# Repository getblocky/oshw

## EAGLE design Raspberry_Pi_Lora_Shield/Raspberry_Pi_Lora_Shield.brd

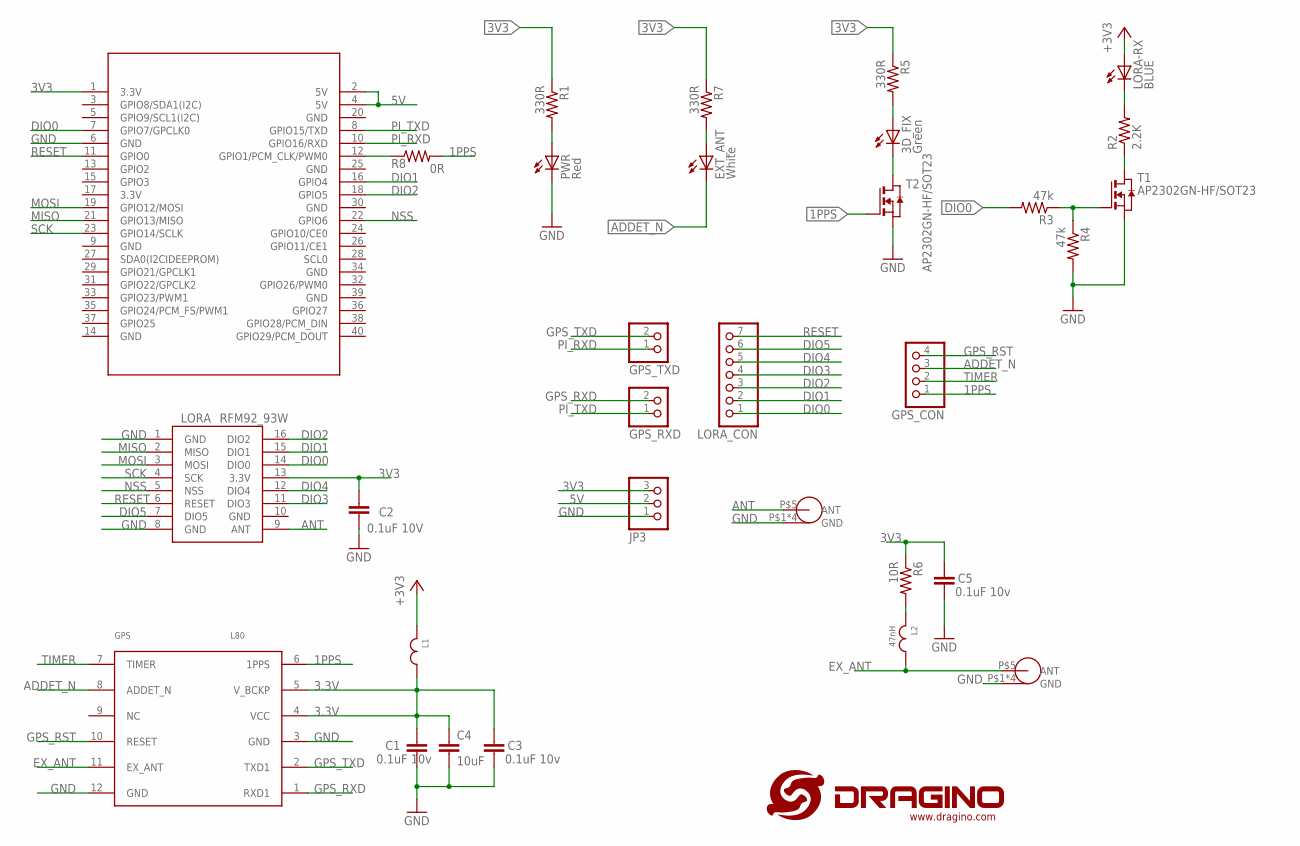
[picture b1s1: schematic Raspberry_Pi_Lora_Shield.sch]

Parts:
3D_FIX: Green; CHIPLED_0603
C1, C3, C5: 0.1uF 10v; C0603
C2: 0.1uF 10V; C0603
C4: 10uF; C1206K
EXT_ANT: White; CHIPLED_0603
GPS: L80
GPS_ANT: NL; SMA-KE
GPS_CON: PINHD-1X4; 1X04
GPS_RXD: PINHD-1X2; 1X02
GPS_TXD: PINHD-1X2; 1X02
JP3: PINHD-1X3; 1X03
L1: JLC-PZ2012D800-3R0TF; C0805
L2: 47nH; C0402
LORA: RFM92_93W
LORA-RX: BLUE; CHIPLED_0603
LORA_ANT: SMA-KE
LORA_CON: PINHD-1X7; 1X07
PWR: Red; CHIPLED_0603
R1, R5, R7: 330R; R0603
R2: 2.2K; R0603
R3, R4: 47k; R0603
R6: 10R; R0603
R8: 0R; R0805
T1, T2: AP2302GN-HF/SOT23; SOT-23
U$1: LOGO-NEW; LOGO-SILK-NEW
U$2: RPILORASHIELD

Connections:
1PPS: GPS.6 (1PPS), GPS_CON.1, R8.2, T2.3 (G)
3.3V: C1.2, C3.2, C4.1, GPS.4 (VCC), GPS.5 (V_BCKP), L1.2
3V3: C2.2, C5.2, JP3.3, L1.1, LORA.13 (3.3V), LORA-RX.A, R1.1, R5.1, R6.1, R7.1, U$2.1 (3.3V)
5V: JP3.2, U$2.2 (5V), U$2.4 (5V)
/RESET: R2.1, T1.1 (D)
ADDET_N: EXT_ANT.C, GPS.8 (ADDET_N), GPS_CON.3
ANT: LORA.9 (ANT), LORA_ANT.P$5 (ANT)
DIO0: LORA.14 (DIO0), LORA_CON.1, R3.2, U$2.7 (GPIO7/GPCLK0)
DIO1: LORA.15 (DIO1), LORA_CON.2, U$2.16 (GPIO4)
DIO2: LORA.16 (DIO2), LORA_CON.3, U$2.18 (GPIO5)
DIO3: LORA.11 (DIO3), LORA_CON.4
DIO4: LORA.12 (DIO4), LORA_CON.5
DIO5: LORA.7 (DIO5), LORA_CON.6
EX_ANT: GPS.11 (EX_ANT), GPS_ANT.P$5 (ANT), L2.2
GND: C1.1, C2.1, C3.1, C4.2, C5.1, GPS.3 (GND), GPS.12 (GND), GPS_ANT.P$1 (GND), GPS_ANT.P$2 (GND), GPS_ANT.P$3 (GND), GPS_ANT.P$4 (GND), JP3.1, LORA.1 (GND), LORA.8 (GND), LORA.10 (GND), LORA_ANT.P$1 (GND), LORA_ANT.P$2 (GND), LORA_ANT.P$3 (GND), LORA_ANT.P$4 (GND), PWR.C, R4.2, T1.2 (S), T2.2 (S), U$2.6 (GND)
GPS_RST: GPS.10 (RESET), GPS_CON.4
GPS_RXD: GPS.1 (RXD1), GPS_RXD.2
GPS_TXD: GPS.2 (TXD1), GPS_TXD.2
MISO: LORA.2 (MISO), U$2.21 (GPIO13/MISO)
MOSI: LORA.3 (MOSI), U$2.19 (GPIO12/MOSI)
unnamed: R3.1, R4.1, T1.3 (G)
unnamed: 3D_FIX.A, R5.2
unnamed: 3D_FIX.C, T2.1 (D)
unnamed: L2.1, R6.2
unnamed: EXT_ANT.A, R7.2
unnamed: PWR.A, R1.2
unnamed: R8.1, U$2.12 (GPIO1/PCM_CLK/PWM0)
unnamed: LORA-RX.C, R2.2
NSS: LORA.5 (NSS), U$2.22 (GPIO6)
PI_RXD: GPS_TXD.1, U$2.10 (GPIO16/RXD)
PI_TXD: GPS_RXD.1, U$2.8 (GPIO15/TXD)
RESET: LORA.6 (RESET), LORA_CON.7, U$2.11 (GPIO0)
SCK: LORA.4 (SCK), U$2.23 (GPIO14/SCLK)
TIMER: GPS.7 (TIMER), GPS_CON.2

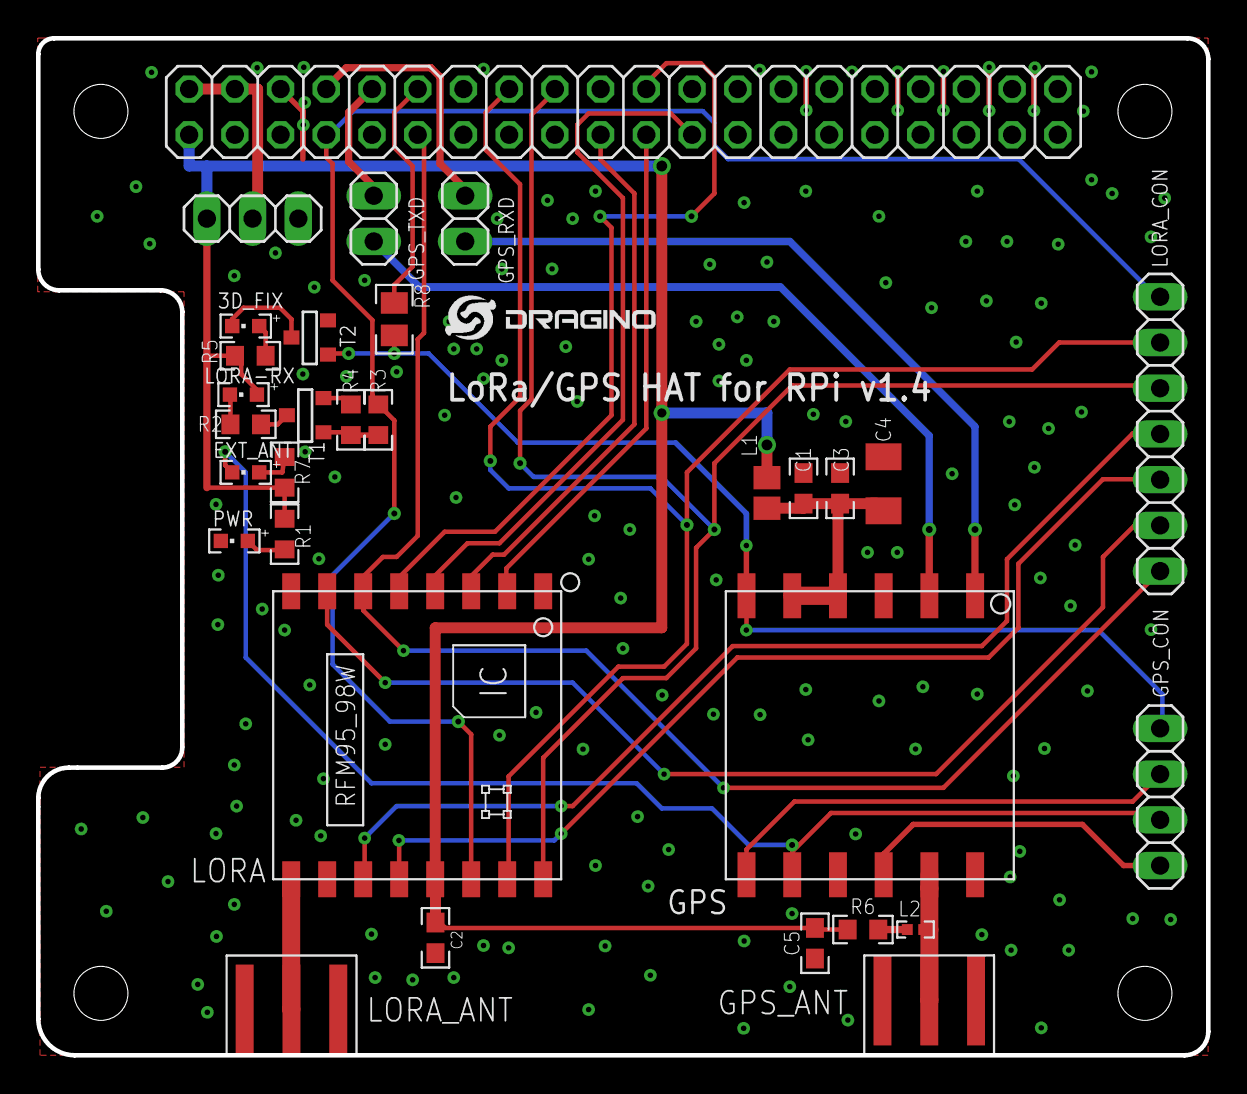
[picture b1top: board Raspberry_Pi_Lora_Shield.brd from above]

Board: 2 copper layers, 65.0 x 56.5 mm, 33 parts (1 on the bottom side), 34 nets.

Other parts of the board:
U$3: BLOCKY_LOGO

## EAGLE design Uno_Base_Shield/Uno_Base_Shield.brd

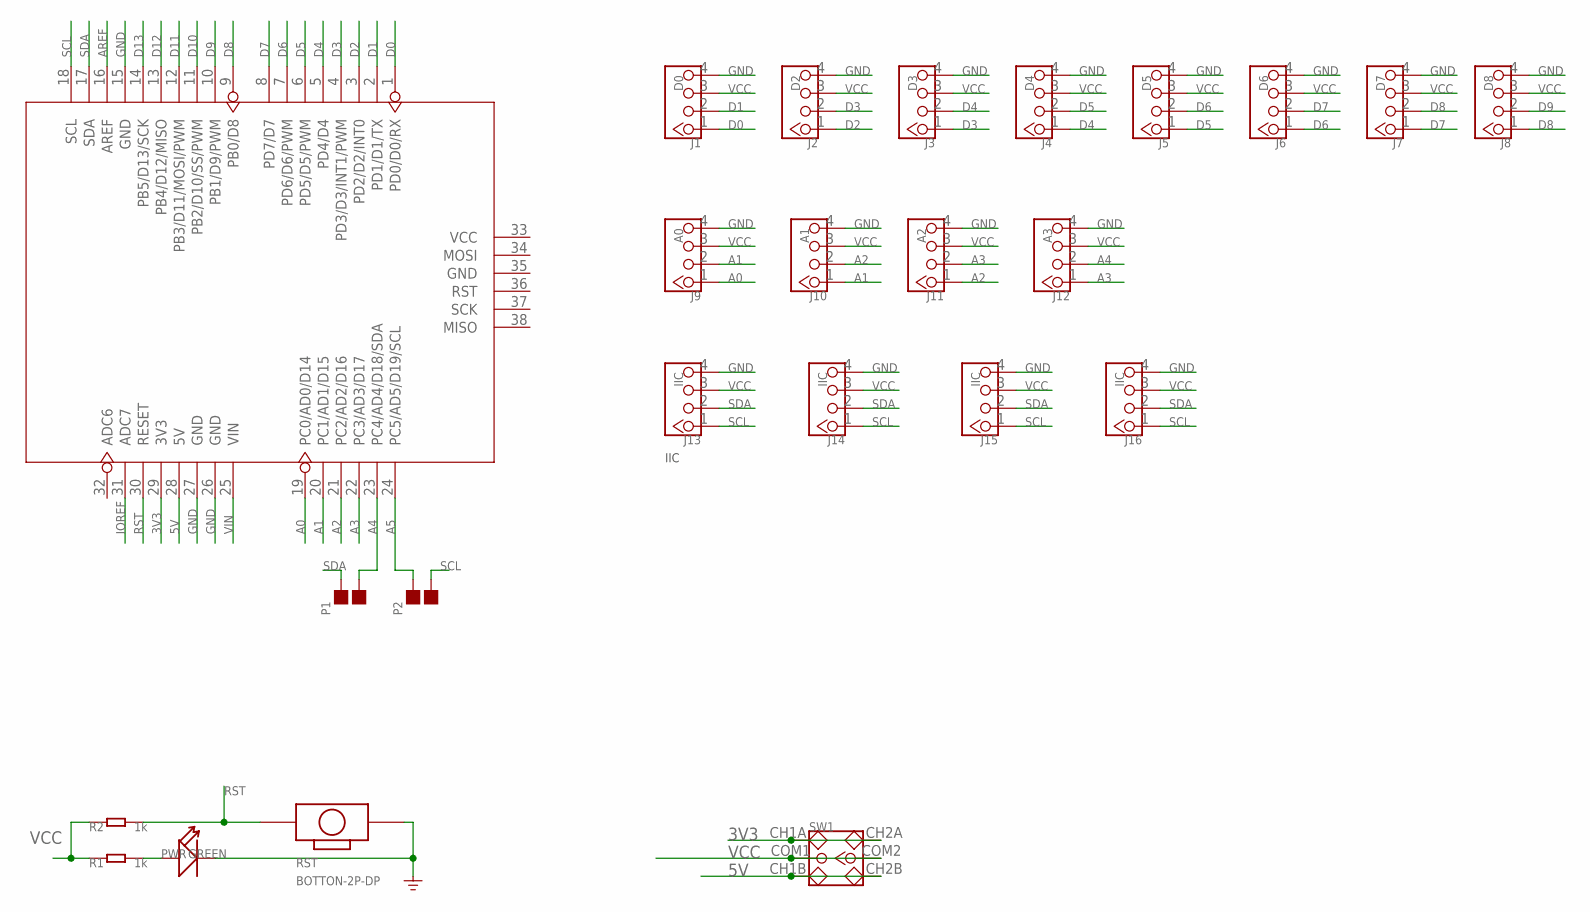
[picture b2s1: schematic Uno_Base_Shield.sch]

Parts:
J1: D0; 4P-2.0
J2: D2; 4P-2.0
J3: D3; 4P-2.0
J4: D4; 4P-2.0
J5: D5; 4P-2.0
J6: D6; 4P-2.0
J7: D7; 4P-2.0
J8: D8; 4P-2.0
J9: A0; 4P-2.0-90D
J10: A1; 4P-2.0-90D
J11: A2; 4P-2.0-90D
J12: A3; 4P-2.0-90D
J13, J14, J15, J16: IIC; 4P-2.0
P1, P2: DNP; 2P-SMD-1.78X1.27
PWR: GREEN; LED-2P-2.54-3MM
R1, R2: 1k; R0603
RST: BOTTON-2P-DP; 2P-7.62X3.56-90D
SW1: SWITCH-2CH-6P'90D'; 6P-2CH-2.5-9.1X3.5X3.2H-90D
U2: DIP Long Blue Female Header; ARDUINO-38P

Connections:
3V3: SW1.CH1A, SW1.CH2A, U2.29 (3V3)
5V: SW1.CH1B, SW1.CH2B, U2.28 (5V)
A0: J9.1, U2.19 (PC0/AD0/D14)
A1: J9.2, J10.1, U2.20 (PC1/AD1/D15)
A2: J10.2, J11.1, U2.21 (PC2/AD2/D16)
A3: J11.2, J12.1, U2.22 (PC3/AD3/D17)
A4: J12.2, P1.1, U2.23 (PC4/AD4/D18/SDA)
A5: P2.2, U2.24 (PC5/AD5/D19/SCL)
AREF: U2.16 (AREF)
D0: J1.1, U2.1 (PD0/D0/RX)
D1: J1.2, U2.2 (PD1/D1/TX)
D2: J2.1, U2.3 (PD2/D2/INT0)
D3: J2.2, J3.1, U2.4 (PD3/D3/INT1/PWM)
D4: J3.2, J4.1, U2.5 (PD4/D4)
D5: J4.2, J5.1, U2.6 (PD5/D5/PWM)
D6: J5.2, J6.1, U2.7 (PD6/D6/PWM)
D7: J6.2, J7.1, U2.8 (PD7/D7)
D8: J7.2, J8.1, U2.9 (PB0/D8)
D9: J8.2, U2.10 (PB1/D9/PWM)
D10: U2.11 (PB2/D10/SS/PWM)
D11: U2.12 (PB3/D11/MOSI/PWM)
D12: U2.13 (PB4/D12/MISO)
D13: U2.14 (PB5/D13/SCK)
GND: J1.4, J2.4, J3.4, J4.4, J5.4, J6.4, J7.4, J8.4, J9.4, J10.4, J11.4, J12.4, J13.4, J14.4, J15.4, J16.4, PWR.K (-), RST.P$2 (2), U2.15 (GND), U2.26 (GND), U2.27 (GND)
IOREF: U2.31 (ADC7)
unnamed: PWR.A (+), R1.2
RST: R2.2, RST.P$1 (1), U2.30 (RESET)
SCL: J13.1, J14.1, J15.1, J16.1, P2.1, U2.18 (SCL)
SDA: J13.2, J14.2, J15.2, J16.2, P1.2, U2.17 (SDA)
VCC: J1.3, J2.3, J3.3, J4.3, J5.3, J6.3, J7.3, J8.3, J9.3, J10.3, J11.3, J12.3, J13.3, J14.3, J15.3, J16.3, R1.1, R2.1, SW1.COM1, SW1.COM2
VIN: U2.25 (VIN)

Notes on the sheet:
IIC

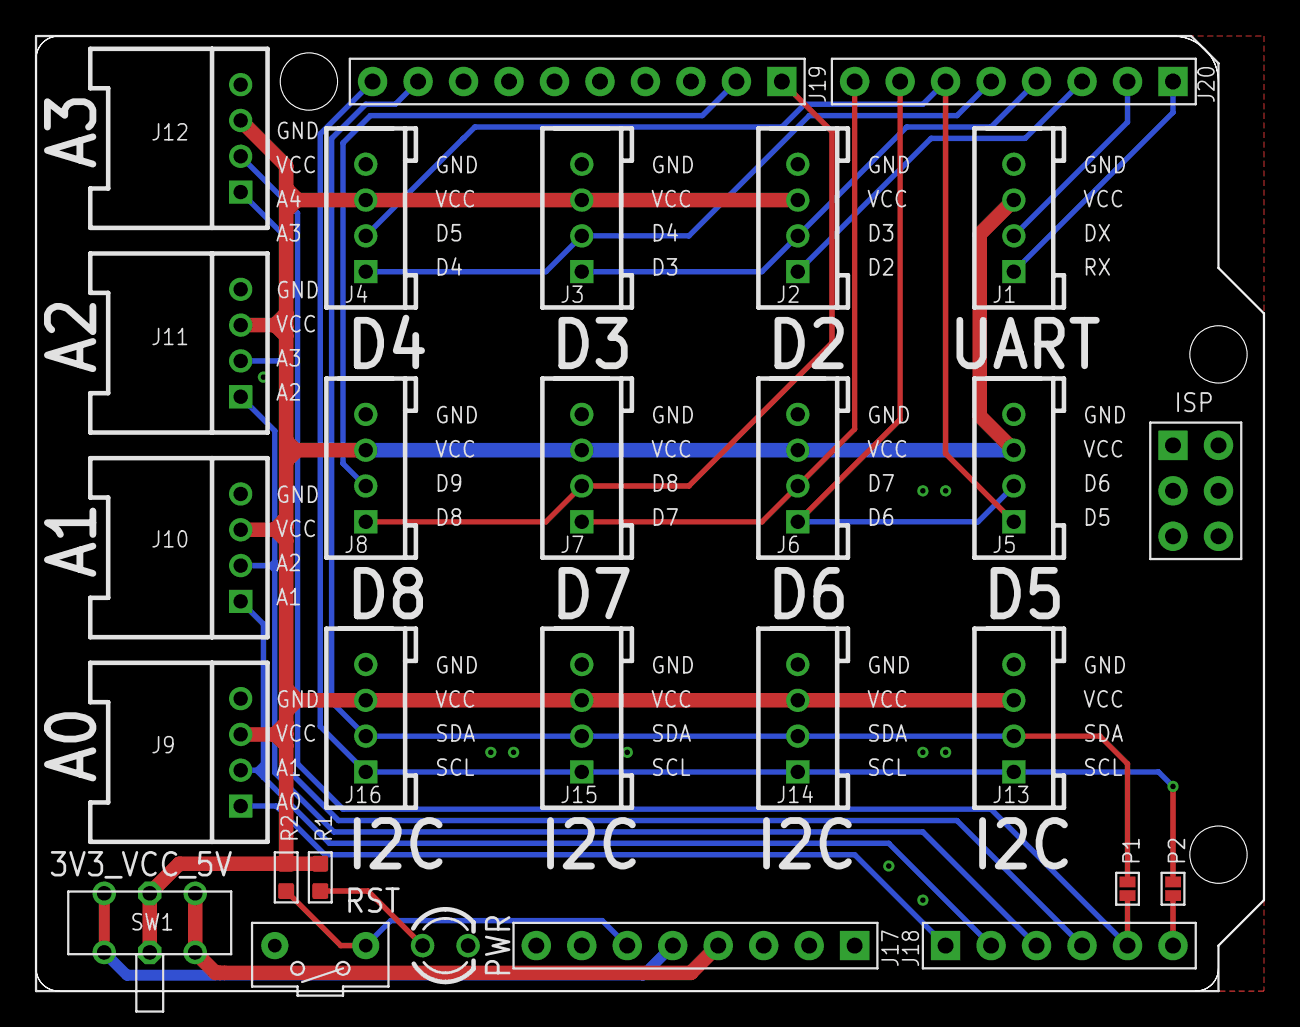
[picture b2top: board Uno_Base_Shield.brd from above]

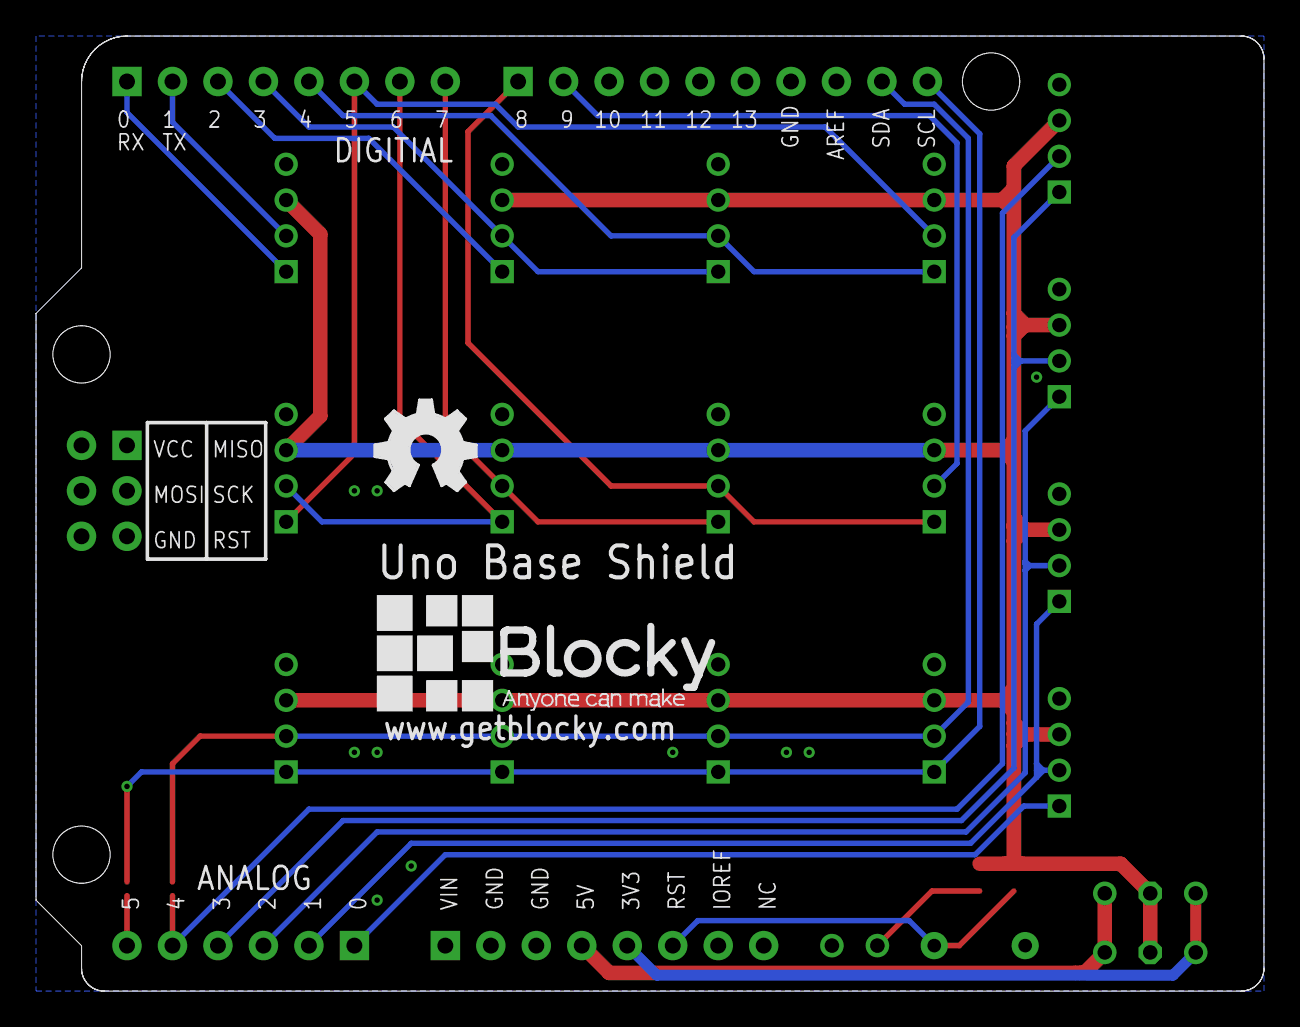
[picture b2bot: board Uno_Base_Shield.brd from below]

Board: 2 copper layers, 68.6 x 53.3 mm, 26 parts (2 on the bottom side), 24 nets.

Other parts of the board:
U$2: OSHW_FILLX200_NOTEXT
U$4: BLOCKY_LOGO

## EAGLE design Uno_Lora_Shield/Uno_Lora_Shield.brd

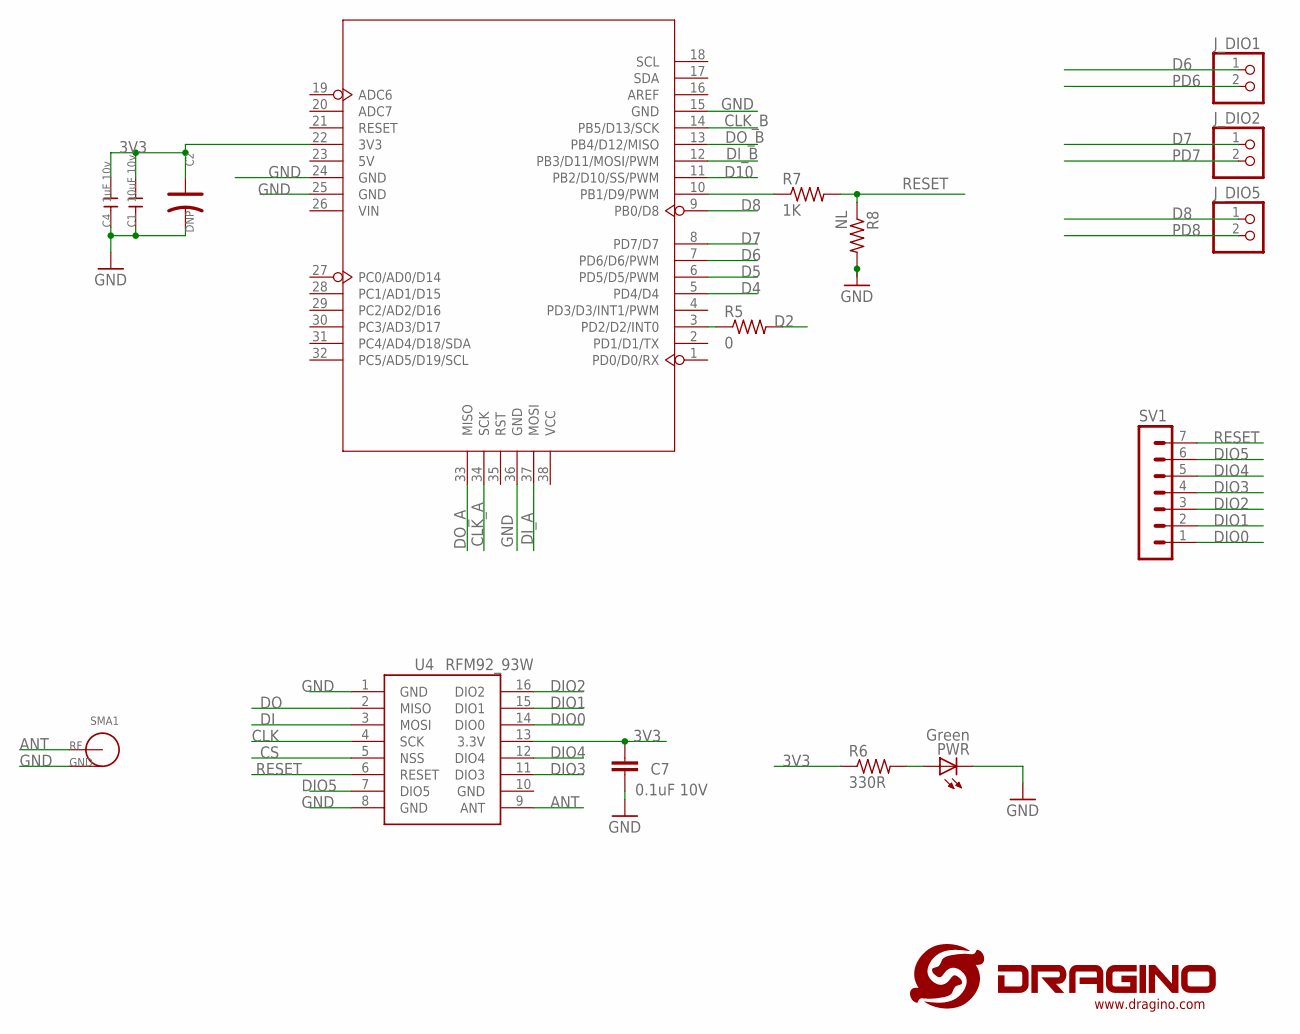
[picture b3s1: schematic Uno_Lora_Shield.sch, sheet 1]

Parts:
C1: 10uF 10v; C0805
C2: DNP; AVX-A
C4: 1uF 10v; C0805
C7: 0.1uF 10V; C0603
J_DIO1, J_DIO2, J_DIO5: PINHD-1X2; 1X02
PWR: Green; CHIP-LED0603
R5: 0; R0603
R6: 330R; R0603
R7: 1K; R0603
R8: NL; R0603
SMA1: SMA-KWE
SV1: MA07-1
U4: RFM92_93W
U5: MOUDLE_ARDUINO-38P328P_NO_VIA; MOUDLE_ARDUINO-328P--
U$1: LOGO-NEW; LOGO-SILK-NEW

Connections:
3V3: C1.2, C2.+, C4.2, C7.2, R6.1, U4.13 (3.3V), U5.22 (3V3); also elsewhere on the board
ANT: SMA1.1 (SIG), U4.9 (ANT)
CLK: U4.4 (SCK); also elsewhere on the board
CLK_A: U5.34 (SCK); also elsewhere on the board
CLK_B: U5.14 (PB5/D13/SCK); also elsewhere on the board
CS: U4.5 (NSS); also elsewhere on the board
D2: R5.2; also elsewhere on the board
D4: U5.5 (PD4/D4); also elsewhere on the board
D5: U5.6 (PD5/D5/PWM); also elsewhere on the board
D6: J_DIO1.1, U5.7 (PD6/D6/PWM)
D7: J_DIO2.1, U5.8 (PD7/D7)
D8: J_DIO5.1, U5.9 (PB0/D8)
D10: U5.11 (PB2/D10/SS/PWM); also elsewhere on the board
DI: U4.3 (MOSI); also elsewhere on the board
DIO0: SV1.1, U4.14 (DIO0); also elsewhere on the board
DIO1: SV1.2, U4.15 (DIO1); also elsewhere on the board
DIO2: SV1.3, U4.16 (DIO2); also elsewhere on the board
DIO3: SV1.4, U4.11 (DIO3)
DIO4: SV1.5, U4.12 (DIO4)
DIO5: SV1.6, U4.7 (DIO5); also elsewhere on the board
DI_A: U5.37 (MOSI); also elsewhere on the board
DI_B: U5.12 (PB3/D11/MOSI/PWM); also elsewhere on the board
DO: U4.2 (MISO); also elsewhere on the board
DO_A: U5.33 (MISO); also elsewhere on the board
DO_B: U5.13 (PB4/D12/MISO); also elsewhere on the board
GND: C1.1, C2.-, C4.1, C7.1, PWR.C, R8.2, SMA1.2 (GND), SMA1.3 (GND), SMA1.4 (GND), SMA1.5 (GND), U4.1 (GND), U4.8 (GND), U4.10 (GND), U5.15 (GND), U5.24 (GND), U5.25 (GND), U5.36 (GND); also elsewhere on the board
unnamed: R5.1, U5.3 (PD2/D2/INT0)
unnamed: PWR.A, R6.2
unnamed: R7.1, U5.10 (PB1/D9/PWM)
PD6: J_DIO1.2; also elsewhere on the board
PD7: J_DIO2.2; also elsewhere on the board
PD8: J_DIO5.2; also elsewhere on the board
RESET: R7.2, R8.1, SV1.7, U4.6 (RESET)

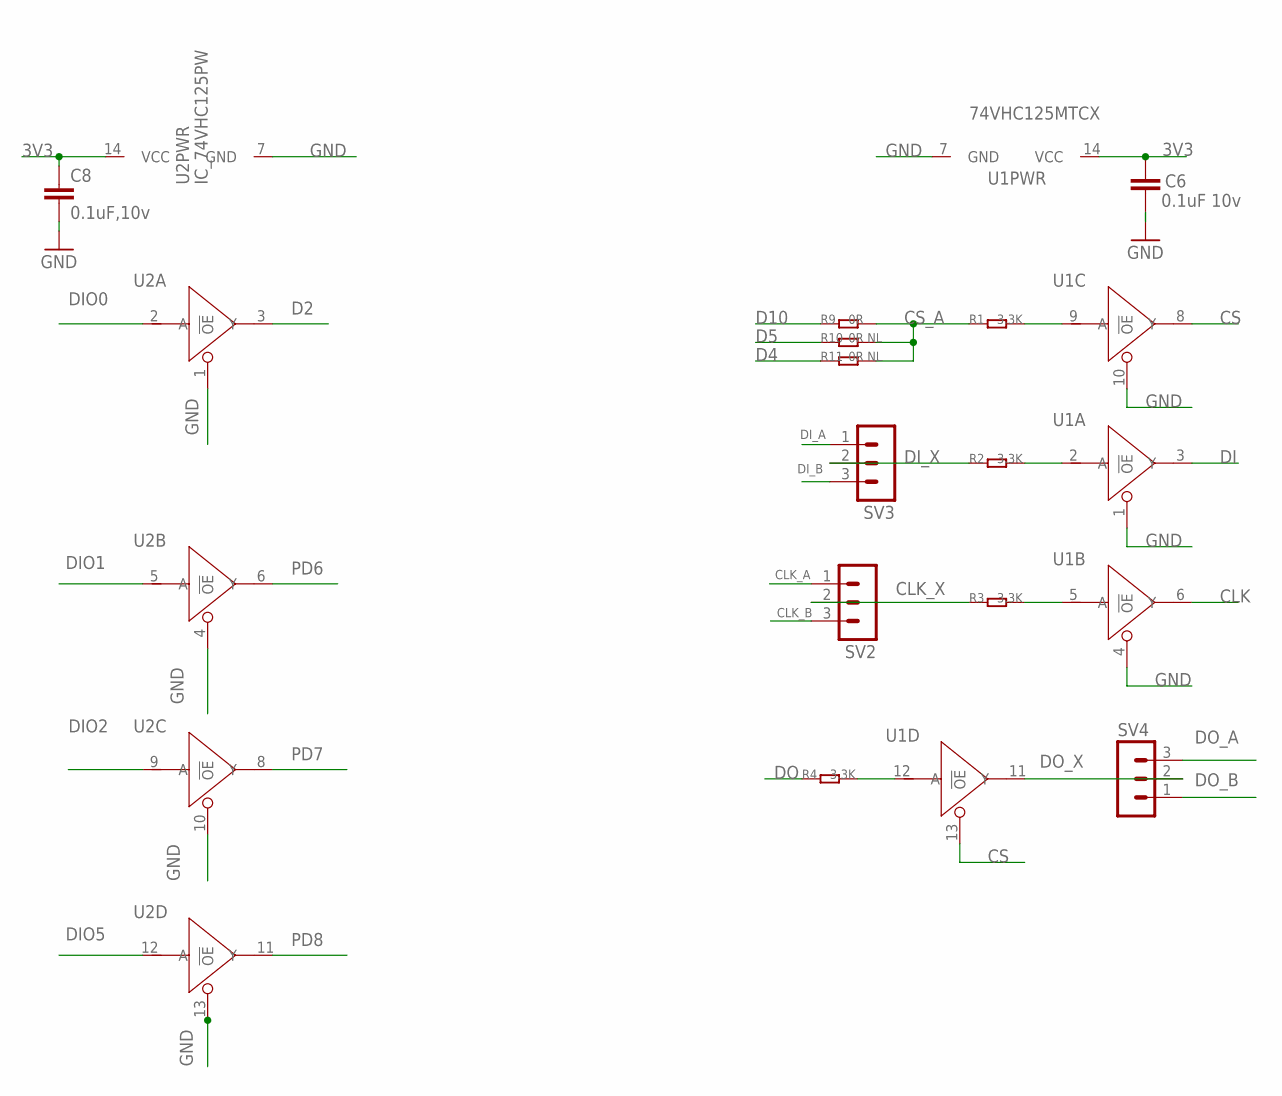
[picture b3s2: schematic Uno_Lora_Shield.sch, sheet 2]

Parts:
C6: 0.1uF 10v; C0805
C8: 0.1uF,10v; C0805
R1, R2, R3, R4: 3.3K; R0603
R9: 0R; R0603
R10, R11: 0R NL; R0603
SV2, SV3, SV4: MA03-1
U1: 74VHC125MTCX; TSSOP14
U2: IC_74VHC125PW; IC_TSSOP14

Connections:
3V3: C6.2, C8.1, U1.14 (VCC), U2.14 (VCC); also elsewhere on the board
CLK: U1.6 (Y); also elsewhere on the board
CLK_A: SV2.1; also elsewhere on the board
CLK_B: SV2.3; also elsewhere on the board
CLK_X: R3.1, SV2.2
CS: U1.8 (Y), U1.13 (!OE); also elsewhere on the board
CS_A: R1.1, R9.2, R10.2, R11.2
D2: U2.3 (Y); also elsewhere on the board
D4: R11.1; also elsewhere on the board
D5: R10.1; also elsewhere on the board
D10: R9.1; also elsewhere on the board
DI: U1.3 (Y); also elsewhere on the board
DIO0: U2.2 (A); also elsewhere on the board
DIO1: U2.5 (A); also elsewhere on the board
DIO2: U2.9 (A); also elsewhere on the board
DIO5: U2.12 (A); also elsewhere on the board
DI_A: SV3.1; also elsewhere on the board
DI_B: SV3.3; also elsewhere on the board
DI_X: R2.1, SV3.2
DO: R4.1; also elsewhere on the board
DO_A: SV4.3; also elsewhere on the board
DO_B: SV4.1; also elsewhere on the board
DO_X: SV4.2, U1.11 (Y)
GND: C6.1, C8.2, U1.1 (!OE), U1.4 (!OE), U1.7 (GND), U1.10 (!OE), U2.1 (!OE), U2.4 (!OE), U2.7 (GND), U2.10 (!OE), U2.13 (!OE); also elsewhere on the board
unnamed: R4.2, U1.12 (A)
unnamed: R3.2, U1.5 (A)
unnamed: R2.2, U1.2 (A)
unnamed: R1.2, U1.9 (A)
PD6: U2.6 (Y); also elsewhere on the board
PD7: U2.8 (Y); also elsewhere on the board
PD8: U2.11 (Y); also elsewhere on the board

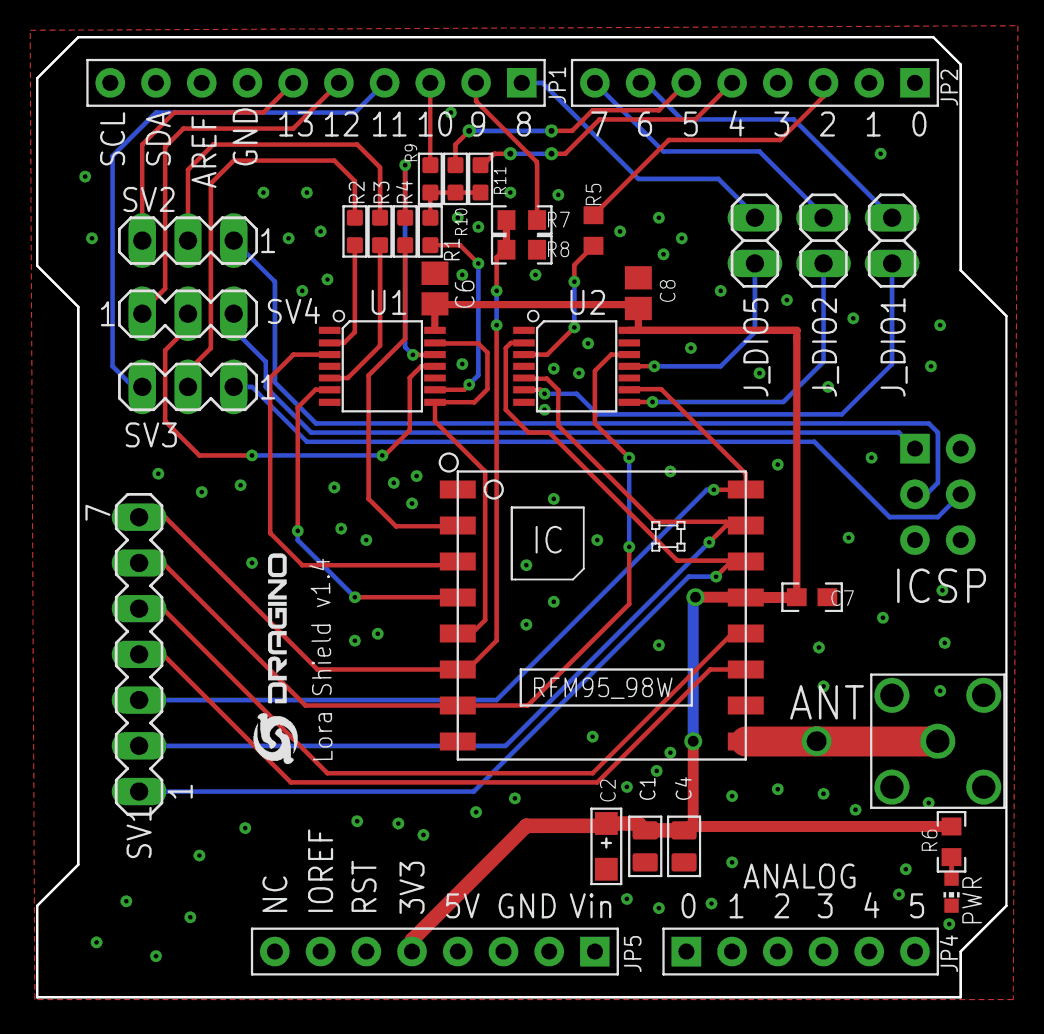
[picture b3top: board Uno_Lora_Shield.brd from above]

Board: 2 copper layers, 53.8 x 53.3 mm, 31 parts (0 on the bottom side), 41 nets.

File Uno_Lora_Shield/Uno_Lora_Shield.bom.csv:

Part,Value,Device,Package,Description,MF,MPN,OC_FARNELL,OC_NEWARK
C1,10uF 10v,C-0805,C0805,Ceramic Capacitors,,,,
C2,DNP,CAP-AVX-A,AVX-A,Electrolytic Capacitors Tantalum Capacitors and Super Capacitors,,,,
C4,1uF 10v,C-0805,C0805,Ceramic Capacitors,,,,
C6,0.1uF 10v,C-EUC0805,C0805,CAPACITOR  European symbol,,,,
C7,0.1uF 10V,C-EUC0402,C0402,CAPACITOR  European symbol,,,,
C8,0.1uF 10v,C-EUC0805,C0805,CAPACITOR  European symbol,,,,
J_DIO1,,PINHD-1X2,1X02,PIN HEADER,,,,
J_DIO2,,PINHD-1X2,1X02,PIN HEADER,,,,
J_DIO5,,PINHD-1X2,1X02,PIN HEADER,,,,
PWR,Green,LEDCHIP-LED0603,CHIP-LED0603,LED,,,,
R1,3.3K,R-0603,R0603,,,,,
R2,3.3K,R-0603,R0603,,,,,
R3,3.3K,R-0603,R0603,,,,,
R4,3.3K,R-0603,R0603,,,,,
R5,0,R-US_R0603,R0603,RESISTOR  American symbol,,,,
R6,330R,R-US_R0402,R0402,RESISTOR  American symbol,,,,
R7,1K,R-US_R0402,R0402,RESISTOR  American symbol,,,,
R8,NL,R-US_R0402,R0402,RESISTOR  American symbol,,,,
R9,0R,R-0603,R0603,,,,,
R10,0R NL,R-0603,R0603,,,,,
R11,0R NL,R-0603,R0603,,,,,
SMA1,SMA-KWE,SMA-KWE,SMA-KWE,http://search.alkon.net/cgi-bin/pdf.pl?pdfname=18276.pdf,,,,
SV1,,MA07-1,MA07-1,PIN HEADER,,,unknown,unknown
SV2,,MA03-1,MA03-1,PIN HEADER,,,unknown,unknown
SV3,,MA03-1,MA03-1,PIN HEADER,,,unknown,unknown
SV4,,MA03-1,MA03-1,PIN HEADER,,,unknown,unknown
U$1,LOGO-NEW,LOGO-NEW,LOGO-SILK-NEW,,,,,
U1,74VHC125MTCX,74VHC125PW,TSSOP14,"Quad Buffer/Line Driver,3-state",,,,
U2,IC_74VHC125PW,IC_74VHC125PW,IC_TSSOP14,"Quad Buffer/Line Driver,3-state",,,,
U4,RFM92_93W,RFM92_93W,RFM92_93W,,,,,
U5,,MOUDLE_ARDUINO-38P328P_NO_VIA,MOUDLE_ARDUINO-328P--,,,,,

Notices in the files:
parts and their libraries:
dragino: http://creativecommons.org/licenses/by-sa/3.0
dragino: Released under the CC Attribution Share-Alike 3.0 License
